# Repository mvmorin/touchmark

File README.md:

# Touchmark
One-piece split, staggered column 40% keyboard. First prototyped on, and inspired by, the [Signum 3.0](http://troyfletcher.net/keyboard_sales.html#signum_30). Low profile and case-less yet still robust enough for travel. Designed in KiCad with symbols and footprints from [keyboard-parts](https://github.com/mvmorin/keyboard-parts) library.

# Features
* Low profile and case-less.
* Standard 4x12 layout.
* Teensy 2.0 and Pro-Micro compatible.
* Full PCB design, including backplate.
* Dedicated MX and Alps plates.
* Flat bottom makes it possible to use it directly on top of a laptop keyboard.

# Construction
The PCB and plate are connected via the switches and standard 2.54 mm pin headers. The Teensy/ProMicro is mounted on the plate itself (or on the base PCB if no plate is used). Only through-hole soldering is necessary and all components are placed on the top of the PCB, leaving the bottom of the keyboard flat. It is recommended to cover the bottom with some soft rubber-like material, I glued on some black shelf liner. It is of course possible to use small rubber feet instead, but this will leave the PCB exposed. It also makes it harder to use on top of a laptop keyboard since the bottom then isn't completely flat.

# PCB Files
The gerber-files for the latest version of the base PCB and the plates are found in the *gerber* directory. For instructions on how to order, see the following [40percent.club](http://www.40percent.club/2017/03/ordering-pcb.html) post. However, please read the **Known Issues** section below and be aware that the tolerances of PCB milling can be large.

# Known Issues
* Alps cutouts are a little tight. About 60% of the cutouts in the test print needed filing.
* Cherry stabilizer cutout are tight but usable.

# Future Updates
Things I'm currently thinking about changing, but who knows when...
* Change from row-high to row-low matrix for easier matrix scan in [tmk](https://github.com/tmk/tmk_keyboard) and to avoid turning on the LED when pressing column 12 keys.
* Increased stagger for pinky keys.
* Change split angle, currently slightly uncomfortable for me. The change of pinky-stagger will probably require a change to the split.
* Remove unused keys on bottom row (2,3,10,11).
* Move thumb clusters up.

# Licenses

This project is released under the [Creative Commons CC-BY-SA 4.0](https://creativecommons.org/licenses/by-sa/4.0/legalcode) license, Copyright (c) Martin Morin 2020.
Some footprints and symbols are based on parts from the [KiCad libraries](https://kicad-pcb.org/libraries/), released under the same [CC-BY-SA 4.0](https://creativecommons.org/licenses/by-sa/4.0/legalcode) license.

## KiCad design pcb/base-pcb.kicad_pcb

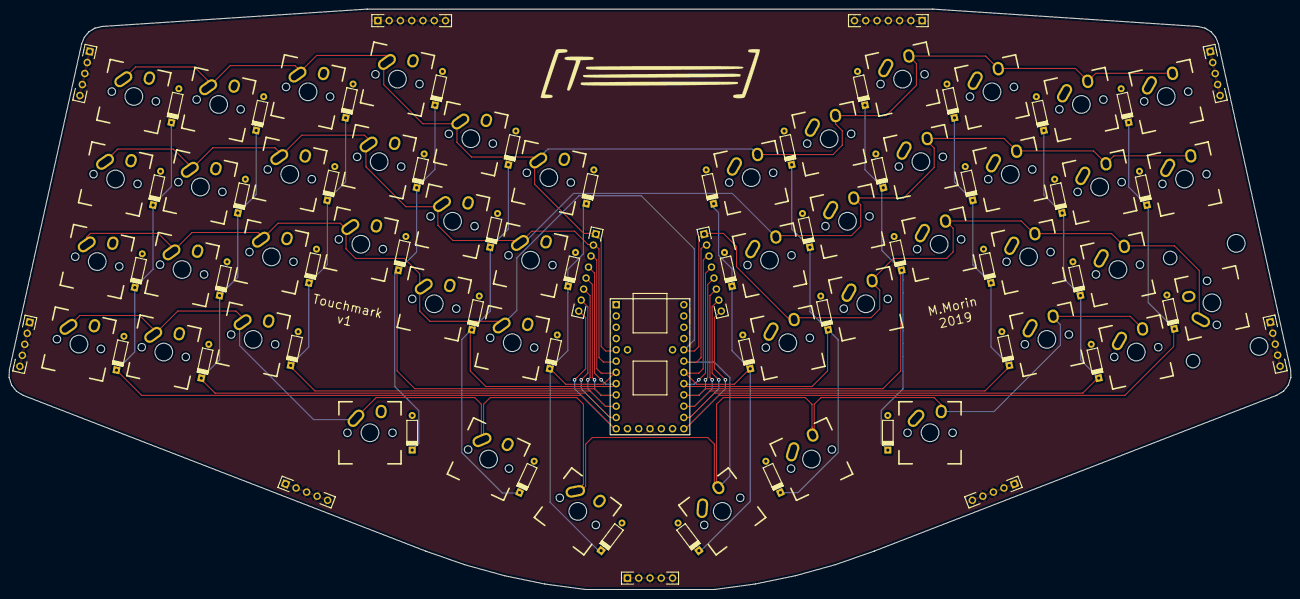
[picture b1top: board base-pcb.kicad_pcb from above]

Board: 2 copper layers, 288.8 x 130.8 mm, 59 parts (0 on the bottom side), 17 nets.

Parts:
J1, J2: Conn_01x08; header_1x08_2.54mm
J3, J5: Conn_01x07; header_1x07_2.54mm
J4, J6, J7, J8, J9, J10, J11: Conn_01x05; header_1x05_2.54mm
KD1, KD2, KD3, KD4, KD5, KD6, KD7, KD8, KD9, KD10, KD11, KD12, KD13, KD14, KD15, KD17, KD18, KD19, KD21, KD22, KD23, KD24: switch-w-diode; mxalps_w_diode_R_100U
KD16, KD20: switch-w-diode; mxalps_w_diode_R_125U
KD25, KD26, KD27, KD28, KD29, KD30, KD31, KD33, KD34, KD35, KD37, KD38, KD39, KD40, KD41, KD42, KD43, KD44, KD45, KD46: switch-w-diode; mxalps_w_diode_L_100U
KD32, KD36: switch-w-diode; mxalps_w_diode_L_125U
KD47: switch-w-diode; mxalps_w_diode_200U
U1: teensy-2.0; teensy2.0

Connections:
/C0: J1.8, KD1.2, KD2.2, KD3.2, KD4.2, U1.12
/C1: J1.7, KD5.2, KD6.2, KD7.2, KD8.2, U1.11
/C2: J1.6, KD9.2, KD10.2, KD11.2, KD12.2, U1.10
/C3: J1.5, KD13.2, KD14.2, KD15.2, KD16.2, U1.9
/C4: J1.4, KD17.2, KD18.2, KD19.2, KD20.2, U1.8
/C5: J1.3, KD21.2, KD22.2, KD23.2, KD24.2, U1.7
/C6: J2.3, KD25.2, KD26.2, KD27.2, KD28.2, U1.23
/C7: J2.4, KD29.2, KD30.2, KD31.2, KD32.2, U1.22
/C8: J2.5, KD33.2, KD34.2, KD35.2, KD36.2, U1.21
/C9: J2.6, KD37.2, KD38.2, KD39.2, KD40.2, U1.20
/C10: J2.7, KD41.2, KD42.2, KD43.2, KD44.2, U1.19
/C11: J2.8, KD45.2, KD46.2, KD47.2, U1.18
/R0: J1.1, KD1.1, KD5.1, KD9.1, KD13.1, KD17.1, KD21.1, KD25.1, KD29.1, KD33.1, KD37.1, KD41.1, KD45.1, U1.5
/R1: J1.2, KD2.1, KD6.1, KD10.1, KD14.1, KD18.1, KD22.1, KD26.1, KD30.1, KD34.1, KD38.1, KD42.1, KD46.1, U1.6
/R2: J2.1, KD3.1, KD7.1, KD11.1, KD15.1, KD19.1, KD23.1, KD27.1, KD31.1, KD35.1, KD39.1, KD43.1, KD47.1, U1.25
/R3: J2.2, KD4.1, KD8.1, KD12.1, KD16.1, KD20.1, KD24.1, KD28.1, KD32.1, KD36.1, KD40.1, KD44.1, U1.24
GND: J3.1, J3.2, J3.3, J3.4, J3.5, J3.6, J3.7, J4.1, J4.2, J4.3, J4.4, J4.5, J5.1, J5.2, J5.3, J5.4, J5.5, J5.6, J5.7, J6.1, J6.2, J6.3, J6.4, J6.5, J7.1, J7.2, J7.3, J7.4, J7.5, J8.1, J8.2, J8.3, J8.4, J8.5, J9.1, J9.2, J9.3, J9.4, J9.5, J10.1, J10.2, J10.3, J10.4, J10.5, J11.1, J11.2, J11.3, J11.4, J11.5, U1.15

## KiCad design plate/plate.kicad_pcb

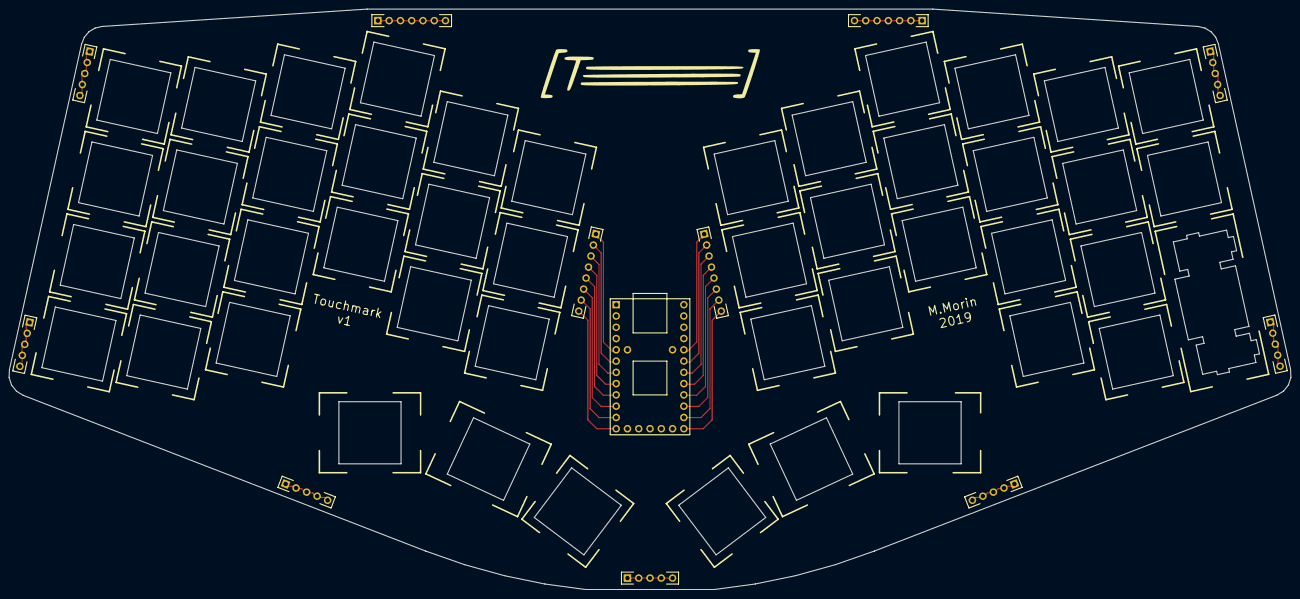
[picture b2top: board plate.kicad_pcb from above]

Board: 2 copper layers, 288.8 x 130.8 mm, 12 parts (0 on the bottom side), 25 nets.

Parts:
J1, J2: Conn_01x08; header_1x08_2.54mm
J3, J5: Conn_01x07; header_1x07_2.54mm
J4, J6, J7, J8, J9, J10, J11: Conn_01x05; header_1x05_2.54mm
U1: teensy-2.0; teensy2.0

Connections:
unnamed: J1.1, U1.5
unnamed: J1.2, U1.6
unnamed: J1.3, U1.7
unnamed: J1.4, U1.8
unnamed: J1.5, U1.9
unnamed: J1.6, U1.10
unnamed: J1.7, U1.11
unnamed: J1.8, U1.12
unnamed: J2.1, U1.25
unnamed: J2.2, U1.24
unnamed: J2.3, U1.23
unnamed: J2.4, U1.22
unnamed: J2.5, U1.21
unnamed: J2.6, U1.20
unnamed: J2.7, U1.19
unnamed: J2.8, U1.18
unnamed: J3.1, J3.2, J3.3, J3.4, J3.5, J3.6, J3.7
unnamed: J4.1, J4.2, J4.3, J4.4, J4.5
unnamed: J5.1, J5.2, J5.3, J5.4, J5.5, J5.6, J5.7
unnamed: J6.1, J6.2, J6.3, J6.4, J6.5
unnamed: J7.1, J7.2, J7.3, J7.4, J7.5
unnamed: J8.1, J8.2, J8.3, J8.4, J8.5
unnamed: J9.1, J9.2, J9.3, J9.4, J9.5
unnamed: J10.1, J10.2, J10.3, J10.4, J10.5
unnamed: J11.1, J11.2, J11.3, J11.4, J11.5

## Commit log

2020-06-13 Add files, library still missing
2020-06-13 Squashed 'keyboard-parts/' content from commit 33f5a16
    git-subtree-dir: keyboard-parts
    git-subtree-split: 33f5a16573515b2b95f2385123d03d383fe1608f
2020-06-14 Add pictures and renders
